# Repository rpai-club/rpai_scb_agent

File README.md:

# Cross Point Project
Software-Configured Breadboard Hardware Targeting Circuit Wiring Error Reduction in ECE Labs.
#
Abstract:
#
The hardware project aims to examine the effectiveness of software-configured wiring compared to traditional manual wiring of breadboards. While both methods use actual hardware, the software-configured approach automates the connections between components, thereby minimizing wiring errors and setup time. The intent is to investigate the impact of each approach on student comprehension, engagement, and error rates. By comparing these two approaches, the project seeks to determine which method better supports student engagement, educational outcomes and reduces frustration associated with complex circuit construction.
#
Introduction:
#
Hands-on experiential learning is a cornerstone of ECE education, typically relying on manual wiring of circuits on solderless breadboards. Using a traditional solderless breadboard as the means for building electronic circuit lab experiments requires the student, in addition to placing components, to manually insert wires to connect together the component pins according to a schematic diagram. These manual translation steps from schematic to hardware can lead to wiring errors in the experimental setup that can obscure circuit principles. While this manual wiring method offers valuable experience in physical component handling and troubleshooting, the extra time needed for debugging and correcting these errors leads to frustration and loss of precious lab time to investigate the circuit concept in question.

The goal is to evaluate the educational benefits and potential drawbacks of these software-configured hardware systems compared to traditional manual wiring. By doing so, it addresses the need for balancing hands-on skills with error minimization and conceptual understanding in electrical engineering education.
#
Analog switch matrix cross point experiment breadboard.
#

Production PCB (Red3 version, instructions for ordering boards can be found in PCB Projects folder)
 
The idea is to computerize the wiring of the breadboard in an effort to reduce student frustration when building complex experiments. Using four analog 16X8 cross point switches wired together into two 32X8 cross points with a fifth switch matrix interconnecting the two smaller arrays into effectively a single 64X16 array.

This breadboard makes real, hardware connections between the 64 breadboard component pins on the board to the16 “jumper” nodes on the board via software commands, instead of needing to manually install jumper wires. The prototype PCB is shown, figure 1, which incorporates two mini 170 pin solderless breadboards, one for each of the 32X8 cross point arrays. There are a combined 68 total component pin locations across both mini breadboards with power distribution strips top and bottom. The two mini breadboards connect to the PCB through pogo pins and so they can be easily removed. It would then be possible to bolt on custom daughter PCBs with whatever components are needed for a given course already installed. Such as CMOS transistor arrays (CD4007) with even some pre-wired sub-circuits like current sources and OTAs.

The combined 64X16 cross point matrix board uses a total of 5 CH446DS 16X8 analog cross point ICs (from China) programed via a RP-2040 micro controller breakout board (Pi Pico or equivalent). Materials cost per board, in quantities of 10 or more, is less than $30 not including the assembly labor.

The board is powered from the Pi Pico USB connection. For powering the experiment circuits, Jumpers can be configured for 0 and +3.3V, 0 and +5V or -5V and +5V power (or 0 and +10V) using an on board isolated 5V DC-DC generator.

LTspice is used to enter the schematic for the experiment. In addition to the standard library symbols a number of supporting schematic library files have been created. Schematic symbols for TO-92 transistors and resistors of various lead spacing are available in the LTspice files.

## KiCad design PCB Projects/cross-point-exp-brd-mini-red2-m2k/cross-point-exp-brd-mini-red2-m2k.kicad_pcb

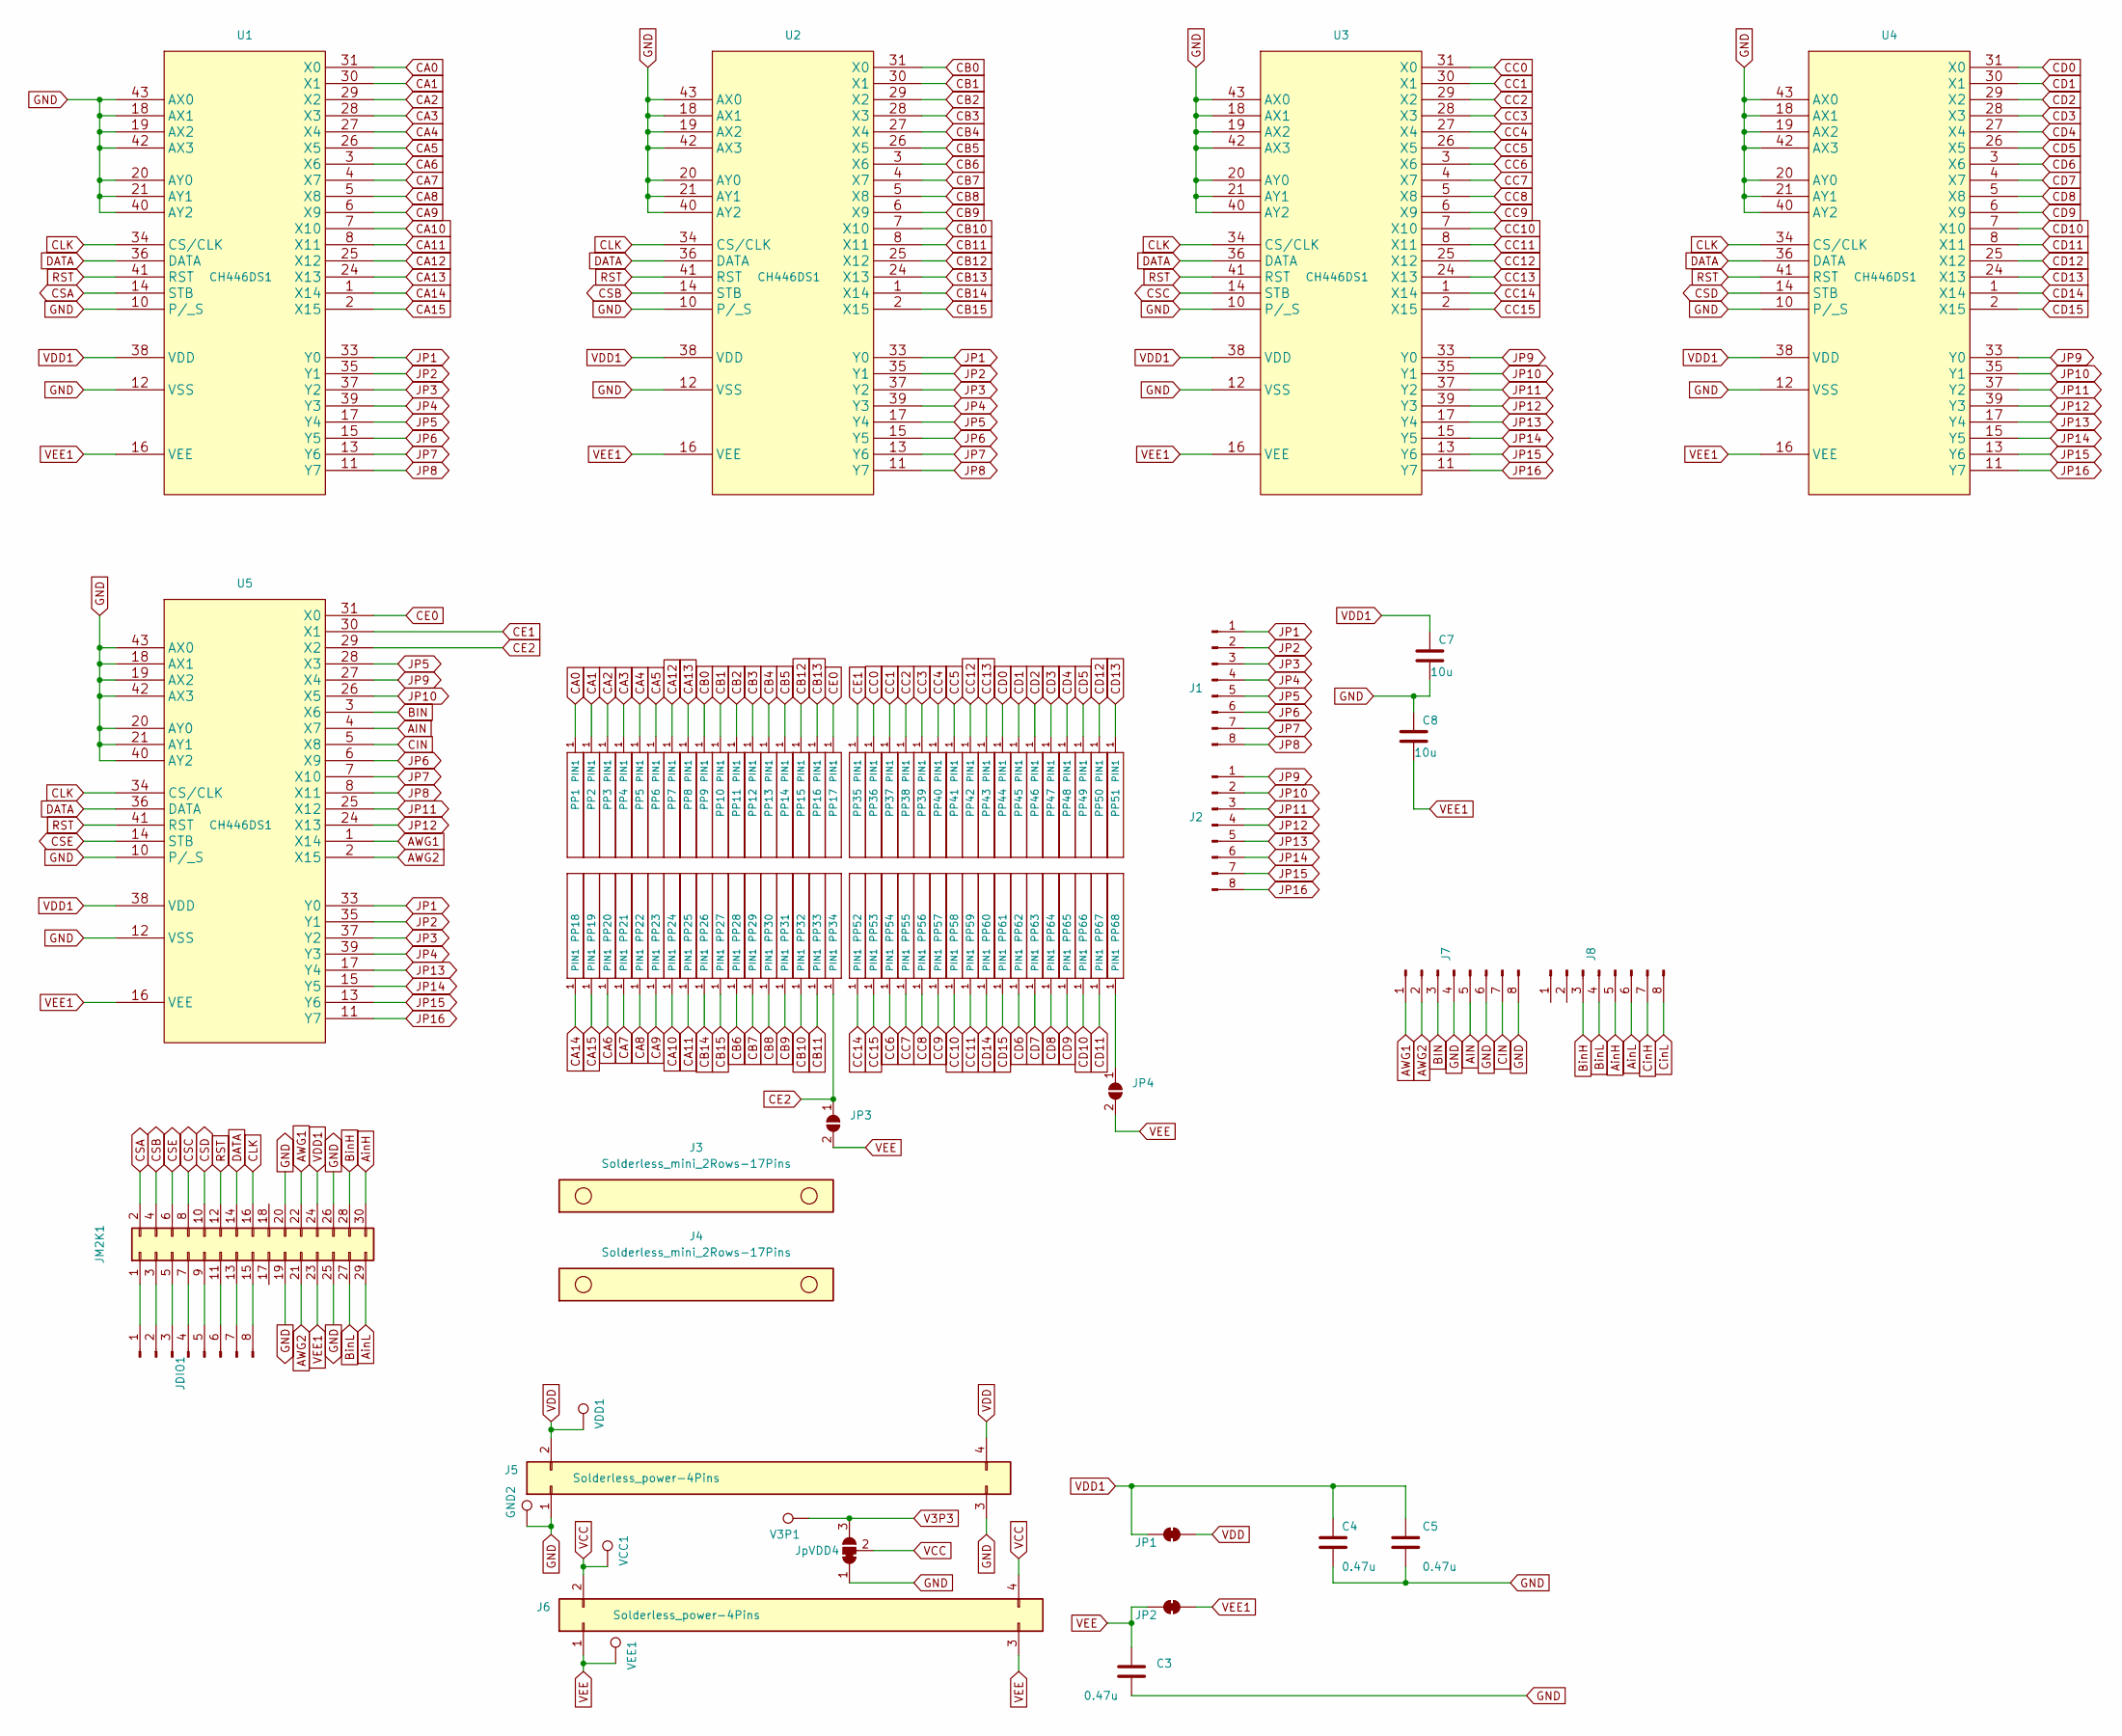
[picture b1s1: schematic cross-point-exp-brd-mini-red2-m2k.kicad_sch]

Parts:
C3, C4, C5: 0.47u; C_1206_3216Metric
C7, C8: 10u; C_1206_3216Metric
GND2: TestPoint; TestPoint_THTPad_D2.0mm_Drill1.0mm
J1, J2, J7, J8: Conn_01x08_Pin; PinHeader_1x08_P2.54mm_Vertical
J3, J4: Solderless_mini_2Rows-17Pins; Solderless_mini_mount_holes_2x17_P2.54mm
J5, J6: Solderless_power-4Pins; Solderless_power_2x4_P2.54mm
JDIO1: Conn_01x08_Pin; PinHeader_1x08_P2.54mm_Vertical
JM2K1: Conn_02x15_Odd_Even; PinHeader_2x15_P2.54mm_Vertical
JP1, JP2: SolderJumper_2_Bridged; SolderJumper-2_P1.3mm_Bridged_RoundedPad1.0x1.5mm
JP3, JP4: SolderJumper_2_Open; SolderJumper-2_P1.3mm_Open_RoundedPad1.0x1.5mm
JpVDD4: Conn_01x03_Pin; SolderJumper-3_P1.3mm_Bridged12_RoundedPad1.0x1.5mm_NumberL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
PP1, PP2, PP3, PP4, PP5, PP6, PP7, PP8, PP9, PP10, PP11, PP12, PP13, PP14, PP15, PP16, PP17, PP18, PP19, PP20, PP21, PP22, PP23, PP24, PP25, PP26, PP27, PP28, PP29, PP30, PP31, PP32, PP33, PP34, PP35, PP36, PP37, PP38, PP39, PP40, PP41, PP42, PP43, PP44, PP45, PP46, PP47, PP48, PP49, PP50, PP51, PP52, PP53, PP54, PP55, PP56, PP57, PP58, PP59, PP60, PP61, PP62, PP63, PP64, PP65, PP66, PP67, PP68: POGO_PIN_01X01_70-9150; MF_Connectors-POGO_PIN_70-9150
U1, U2, U3, U4, U5: CH446DS1; LQFP44_Tight
V3P1: TestPoint; TestPoint_THTPad_D2.0mm_Drill1.0mm
VCC1: TestPoint; TestPoint_THTPad_D2.0mm_Drill1.0mm
VDD1: TestPoint; TestPoint_THTPad_D2.0mm_Drill1.0mm
VEE1: TestPoint; TestPoint_THTPad_D2.0mm_Drill1.0mm

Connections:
AIN: J7.5, U5.4 (X7)
AWG1: J7.1, JM2K1.22, U5.1 (X14)
AWG2: J7.2, JM2K1.21, U5.2 (X15)
AinH: J8.5, JM2K1.30
AinL: J8.6, JM2K1.29
BIN: J7.3, U5.3 (X6)
BinH: J8.3, JM2K1.28
BinL: J8.4, JM2K1.27
CA0: PP1.1 (PIN1), U1.31 (X0)
CA1: PP2.1 (PIN1), U1.30 (X1)
CA2: PP3.1 (PIN1), U1.29 (X2)
CA3: PP4.1 (PIN1), U1.28 (X3)
CA4: PP5.1 (PIN1), U1.27 (X4)
CA5: PP6.1 (PIN1), U1.26 (X5)
CA6: PP20.1 (PIN1), U1.3 (X6)
CA7: PP21.1 (PIN1), U1.4 (X7)
CA8: PP22.1 (PIN1), U1.5 (X8)
CA9: PP23.1 (PIN1), U1.6 (X9)
CA10: PP24.1 (PIN1), U1.7 (X10)
CA11: PP25.1 (PIN1), U1.8 (X11)
CA12: PP7.1 (PIN1), U1.25 (X12)
CA13: PP8.1 (PIN1), U1.24 (X13)
CA14: PP18.1 (PIN1), U1.1 (X14)
CA15: PP19.1 (PIN1), U1.2 (X15)
CB0: PP9.1 (PIN1), U2.31 (X0)
CB1: PP10.1 (PIN1), U2.30 (X1)
CB2: PP11.1 (PIN1), U2.29 (X2)
CB3: PP12.1 (PIN1), U2.28 (X3)
CB4: PP13.1 (PIN1), U2.27 (X4)
CB5: PP14.1 (PIN1), U2.26 (X5)
CB6: PP28.1 (PIN1), U2.3 (X6)
CB7: PP29.1 (PIN1), U2.4 (X7)
CB8: PP30.1 (PIN1), U2.5 (X8)
CB9: PP31.1 (PIN1), U2.6 (X9)
CB10: PP32.1 (PIN1), U2.7 (X10)
CB11: PP33.1 (PIN1), U2.8 (X11)
CB12: PP15.1 (PIN1), U2.25 (X12)
CB13: PP16.1 (PIN1), U2.24 (X13)
CB14: PP26.1 (PIN1), U2.1 (X14)
CB15: PP27.1 (PIN1), U2.2 (X15)
CC0: PP36.1 (PIN1), U3.31 (X0)
CC1: PP37.1 (PIN1), U3.30 (X1)
CC2: PP38.1 (PIN1), U3.29 (X2)
CC3: PP39.1 (PIN1), U3.28 (X3)
CC4: PP40.1 (PIN1), U3.27 (X4)
CC5: PP41.1 (PIN1), U3.26 (X5)
CC6: PP54.1 (PIN1), U3.3 (X6)
CC7: PP55.1 (PIN1), U3.4 (X7)
CC8: PP56.1 (PIN1), U3.5 (X8)
CC9: PP57.1 (PIN1), U3.6 (X9)
CC10: PP58.1 (PIN1), U3.7 (X10)
CC11: PP59.1 (PIN1), U3.8 (X11)
CC12: PP42.1 (PIN1), U3.25 (X12)
CC13: PP43.1 (PIN1), U3.24 (X13)
CC14: PP52.1 (PIN1), U3.1 (X14)
CC15: PP53.1 (PIN1), U3.2 (X15)
CD0: PP44.1 (PIN1), U4.31 (X0)
CD1: PP45.1 (PIN1), U4.30 (X1)
CD2: PP46.1 (PIN1), U4.29 (X2)
CD3: PP47.1 (PIN1), U4.28 (X3)
CD4: PP48.1 (PIN1), U4.27 (X4)
CD5: PP49.1 (PIN1), U4.26 (X5)
CD6: PP62.1 (PIN1), U4.3 (X6)
CD7: PP63.1 (PIN1), U4.4 (X7)
CD8: PP64.1 (PIN1), U4.5 (X8)
CD9: PP65.1 (PIN1), U4.6 (X9)
CD10: PP66.1 (PIN1), U4.7 (X10)
CD11: PP67.1 (PIN1), U4.8 (X11)
CD12: PP50.1 (PIN1), U4.25 (X12)
CD13: PP51.1 (PIN1), U4.24 (X13)
CD14: PP60.1 (PIN1), U4.1 (X14)
CD15: PP61.1 (PIN1), U4.2 (X15)
CE0: PP17.1 (PIN1), U5.31 (X0)
CE1: PP35.1 (PIN1), U5.30 (X1)
CE2: JP3.1 (A), PP34.1 (PIN1), U5.29 (X2)
CIN: J7.7, U5.5 (X8)
CLK: JM2K1.16, U1.34 (CS/CLK), U2.34 (CS/CLK), U3.34 (CS/CLK), U4.34 (CS/CLK), U5.34 (CS/CLK)
CSA: JM2K1.2, U1.14 (STB)
CSB: JM2K1.4, U2.14 (STB)
CSC: JM2K1.8, U3.14 (STB)
CSD: JM2K1.10, U4.14 (STB)
CSE: JM2K1.6, U5.14 (STB)
CinH: J8.7
CinL: J8.8
DATA: JM2K1.14, U1.36 (DATA), U2.36 (DATA), U3.36 (DATA), U4.36 (DATA), U5.36 (DATA)
GND: C3.2, C4.2, C5.2, C7.2, C8.1, GND2.1, J5.1, J5.3, J7.4, J7.6, J7.8, JM2K1.19, JM2K1.20, JM2K1.25, JM2K1.26, JpVDD4.1 (A), U1.10 (P/_S), U1.12 (VSS), U1.18 (AX1), U1.19 (AX2), U1.20 (AY0), U1.21 (AY1), U1.40 (AY2), U1.42 (AX3), U1.43 (AX0), U2.10 (P/_S), U2.12 (VSS), U2.18 (AX1), U2.19 (AX2), U2.20 (AY0), U2.21 (AY1), U2.40 (AY2), U2.42 (AX3), U2.43 (AX0), U3.10 (P/_S), U3.12 (VSS), U3.18 (AX1), U3.19 (AX2), U3.20 (AY0), U3.21 (AY1), U3.40 (AY2), U3.42 (AX3), U3.43 (AX0), U4.10 (P/_S), U4.12 (VSS), U4.18 (AX1), U4.19 (AX2), U4.20 (AY0), U4.21 (AY1), U4.40 (AY2), U4.42 (AX3), U4.43 (AX0), U5.10 (P/_S), U5.12 (VSS), U5.18 (AX1), U5.19 (AX2), U5.20 (AY0), U5.21 (AY1), U5.40 (AY2), U5.42 (AX3), U5.43 (AX0); also elsewhere on the board
JP1: J1.1, U1.33 (Y0), U2.33 (Y0), U5.33 (Y0)
JP2: J1.2, U1.35 (Y1), U2.35 (Y1), U5.35 (Y1)
JP3: J1.3, U1.37 (Y2), U2.37 (Y2), U5.37 (Y2)
JP4: J1.4, U1.39 (Y3), U2.39 (Y3), U5.39 (Y3)
JP5: J1.5, U1.17 (Y4), U2.17 (Y4), U5.28 (X3)
JP6: J1.6, U1.15 (Y5), U2.15 (Y5), U5.6 (X9)
JP7: J1.7, U1.13 (Y6), U2.13 (Y6), U5.7 (X10)
JP8: J1.8, U1.11 (Y7), U2.11 (Y7), U5.8 (X11)
JP9: J2.1, U3.33 (Y0), U4.33 (Y0), U5.27 (X4)
JP10: J2.2, U3.35 (Y1), U4.35 (Y1), U5.26 (X5)
JP11: J2.3, U3.37 (Y2), U4.37 (Y2), U5.25 (X12)
JP12: J2.4, U3.39 (Y3), U4.39 (Y3), U5.24 (X13)
JP13: J2.5, U3.17 (Y4), U4.17 (Y4), U5.17 (Y4)
JP14: J2.6, U3.15 (Y5), U4.15 (Y5), U5.15 (Y5)
JP15: J2.7, U3.13 (Y6), U4.13 (Y6), U5.13 (Y6)
JP16: J2.8, U3.11 (Y7), U4.11 (Y7), U5.11 (Y7)
unnamed: JDIO1.1, JM2K1.1
unnamed: JDIO1.2, JM2K1.3
unnamed: JDIO1.3, JM2K1.5
unnamed: JDIO1.4, JM2K1.7
unnamed: JDIO1.5, JM2K1.9
unnamed: JDIO1.6, JM2K1.11
unnamed: JDIO1.7, JM2K1.13
unnamed: JDIO1.8, JM2K1.15
unnamed: JP4.1 (A), PP68.1 (PIN1)
RST: JM2K1.12, U1.41 (RST), U2.41 (RST), U3.41 (RST), U4.41 (RST), U5.41 (RST)
V3P3: JpVDD4.3 (B), V3P1.1
VCC: J6.2, J6.4, JpVDD4.2 (C), VCC1.1
VDD: J5.2, J5.4, JP1.1 (A), VDD1.1
VDD1: C4.1, C5.1, C7.1, JM2K1.24, JP1.2 (B), U1.38 (VDD), U2.38 (VDD), U3.38 (VDD), U4.38 (VDD), U5.38 (VDD)
VEE: C3.1, J6.1, J6.3, JP2.2 (B), JP3.2 (B), JP4.2 (B), VEE1.1
VEE1: C8.2, JM2K1.23, JP2.1 (A), U1.16 (VEE), U2.16 (VEE), U3.16 (VEE), U4.16 (VEE), U5.16 (VEE)

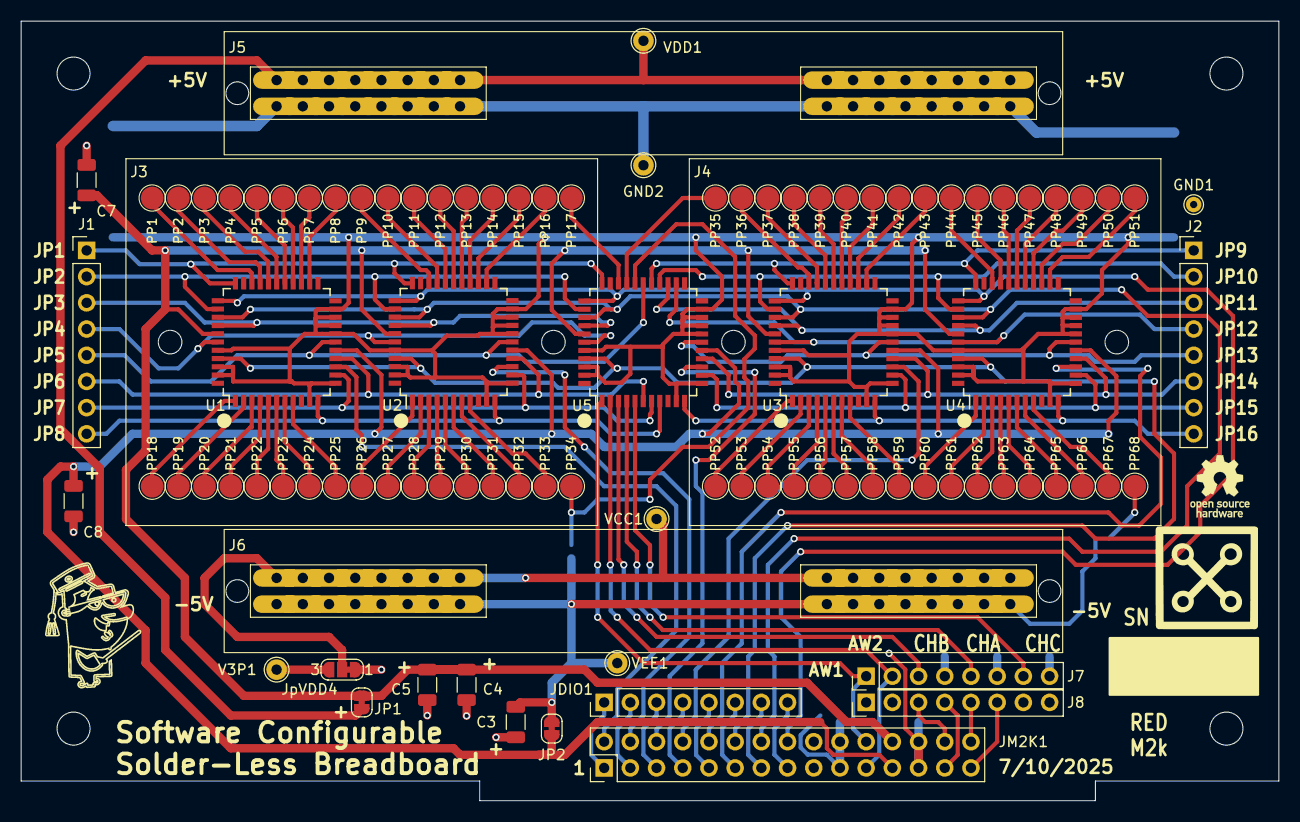
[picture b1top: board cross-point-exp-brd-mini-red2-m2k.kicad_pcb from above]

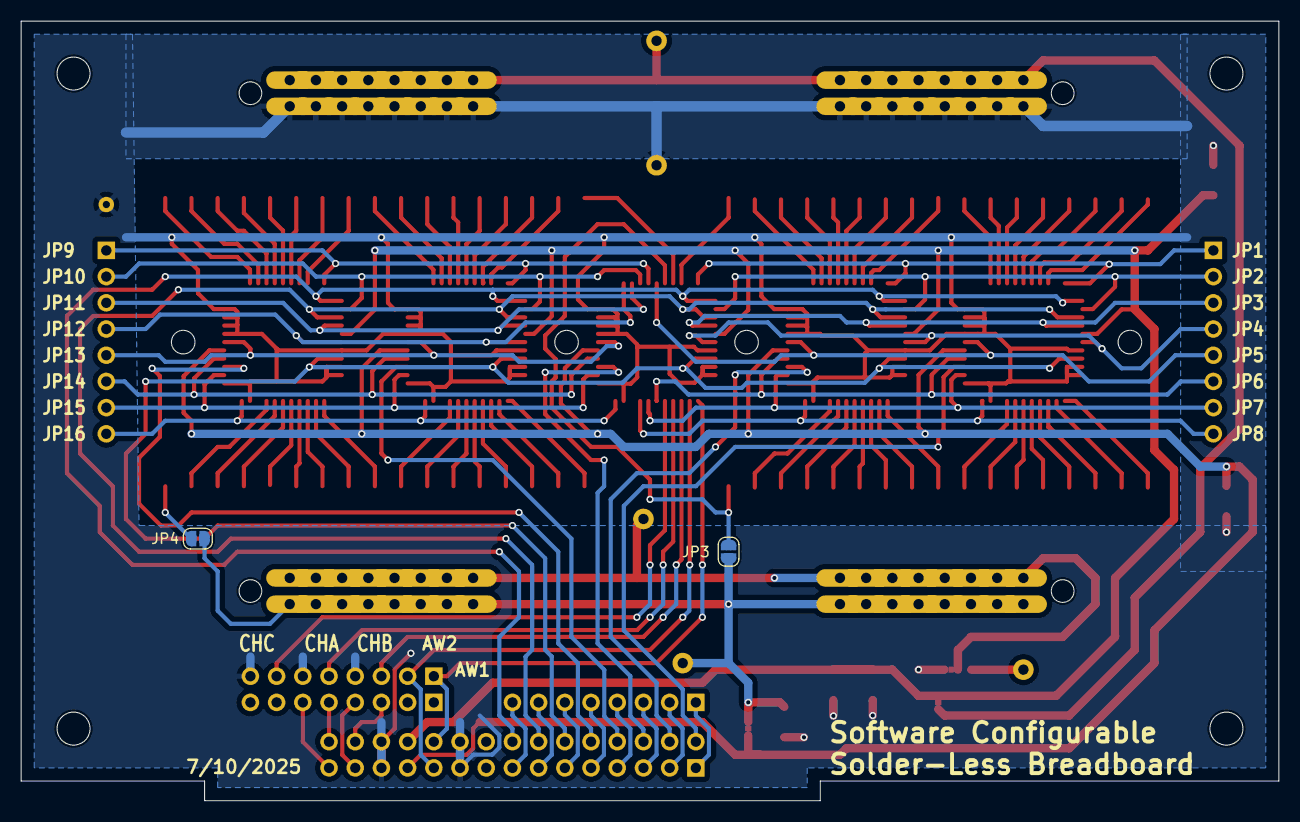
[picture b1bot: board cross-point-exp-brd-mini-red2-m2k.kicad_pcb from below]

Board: 2 copper layers, 121.9 x 75.6 mm, 99 parts (2 on the bottom side), 116 nets.

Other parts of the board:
GND1: TestPoint; TestPoint_THTPad_D1.5mm_Drill0.7mm

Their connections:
GND: GND1.1; also elsewhere on the board

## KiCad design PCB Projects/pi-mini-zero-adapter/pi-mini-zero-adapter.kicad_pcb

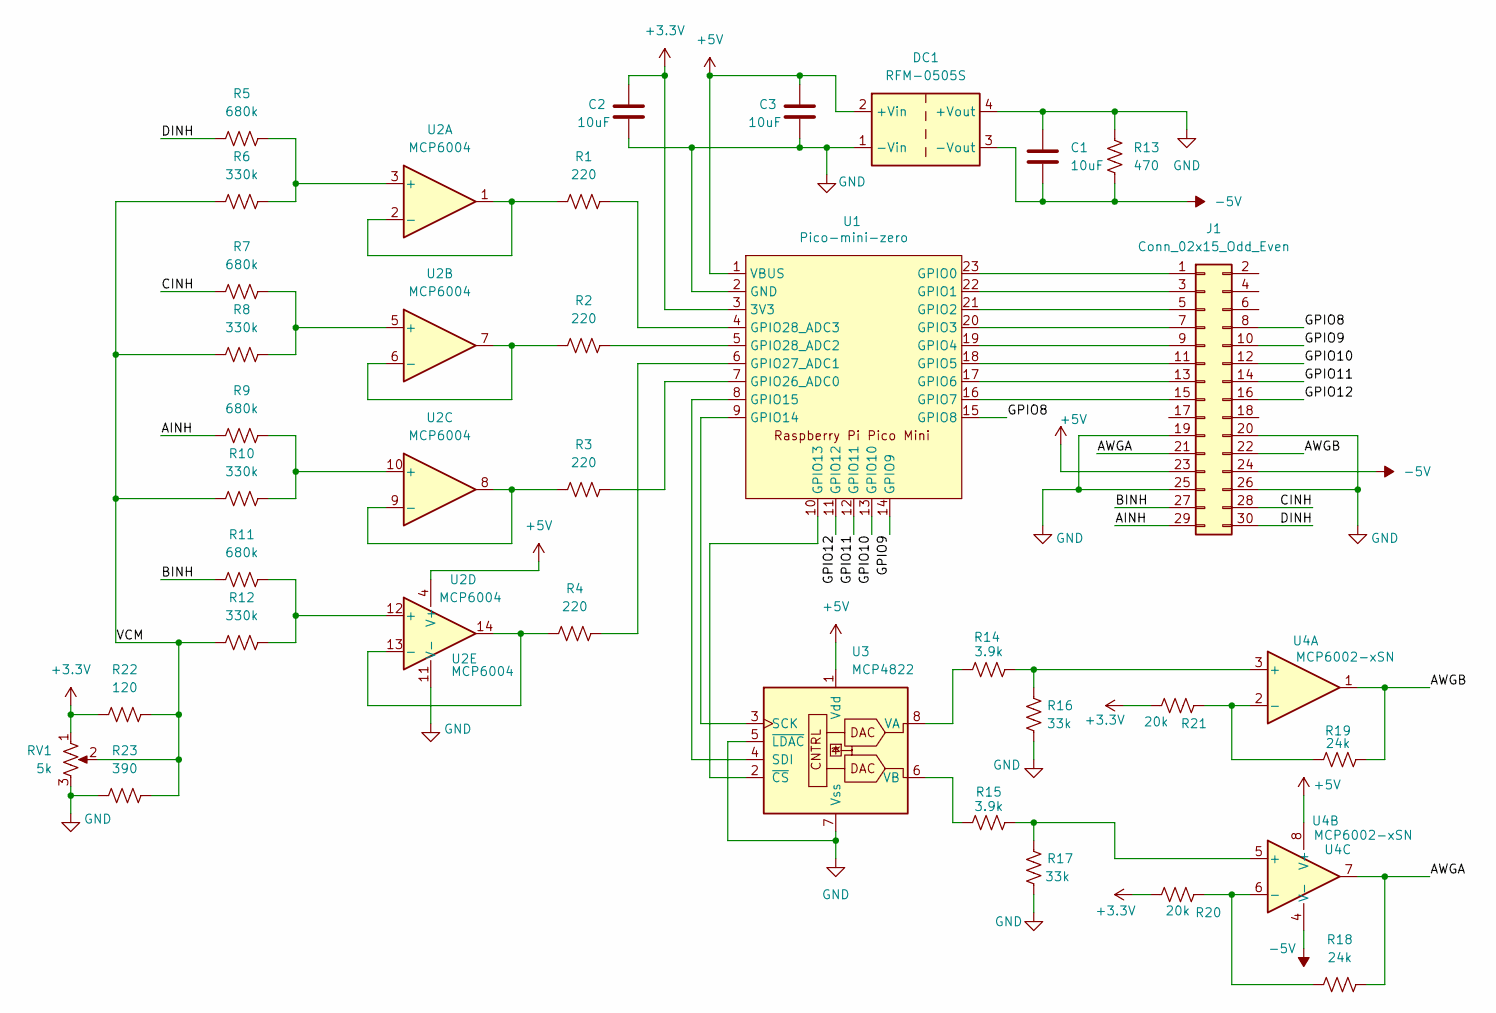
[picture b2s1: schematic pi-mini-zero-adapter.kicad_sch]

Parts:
C1, C2, C3: 10uF; C_1206_3216Metric
DC1: RFM-0505S
J1: Conn_02x15_Odd_Even; PinHeader_2x15_P2.54mm_Horizontal
R1, R2, R3, R4: 220; R_1206_3216Metric
R5, R7, R9, R11: 680k; R_1206_3216Metric
R6, R8, R10, R12: 330k; R_1206_3216Metric
R13: 470; R_1206_3216Metric
R14, R15: 3.9k; R_1206_3216Metric
R16, R17: 33k; R_1206_3216Metric
R18, R19: 24k; R_1206_3216Metric
R20, R21: 20k; R_1206_3216Metric
R22: 120; R_1206_3216Metric
R23: 390; R_1206_3216Metric
RV1: 5k; Potentiometer_Bourns_3386P_Vertical
U1: Pico-mini-zero; RPi_Mini_Zero_SMD_TH
U2: MCP6004; SOIC-14_3.9x8.7mm_P1.27mm
U3: MCP4822; SOIC-8_3.9x4.9mm_P1.27mm
U4: MCP6002-xSN; SO-8_3.9x4.9mm_P1.27mm

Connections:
+3.3V: C2.1, R20.2, R21.2, R22.2, RV1.1, U1.3 (3V3)
+5V: C3.1, DC1.2 (+Vin), J1.23, U1.1 (VBUS), U2.4 (V+), U3.1 (Vdd), U4.8 (V+)
-5V: C1.2, DC1.3 (-Vout), J1.24, R13.2, U4.4 (V-)
/AINH: J1.29, R9.2
/AWGA: J1.21, R18.1, U4.7
/AWGB: J1.22, R19.1, U4.1
/BINH: J1.27, R11.2
/CINH: J1.28, R7.2
/DINH: J1.30, R5.2
/GPIO8: J1.8, U1.15 (GPIO8)
/GPIO9: J1.10, U1.14 (GPIO9)
/GPIO10: J1.12, U1.13 (GPIO10)
/GPIO11: J1.14, U1.12 (GPIO11)
/GPIO12: J1.16, U1.11 (GPIO12)
/VCM: R6.2, R8.2, R10.2, R12.2, R22.1, R23.1, RV1.2
GND: C1.1, C2.2, C3.2, DC1.1 (-Vin), DC1.4 (+Vout), J1.19, J1.20, J1.25, J1.26, R13.1, R16.1, R17.1, R23.2, RV1.3, U1.2 (GND), U2.11 (V-), U3.5 (~LDAC), U3.7 (Vss)
unnamed: J1.1, U1.23 (GPIO0)
unnamed: J1.3, U1.22 (GPIO1)
unnamed: J1.5, U1.21 (GPIO2)
unnamed: J1.7, U1.20 (GPIO3)
unnamed: J1.9, U1.19 (GPIO4)
unnamed: J1.11, U1.18 (GPIO5)
unnamed: J1.13, U1.17 (GPIO6)
unnamed: J1.15, U1.16 (GPIO7)
unnamed: U1.10 (GPIO13), U3.2 (~CS)
unnamed: U1.9 (GPIO14), U3.3 (SCK)
unnamed: U1.8 (GPIO15), U3.4 (SDI)
unnamed: R3.1, U1.7 (GPIO26_ADC0)
unnamed: R4.1, U1.6 (GPIO27_ADC1)
unnamed: R2.1, U1.5 (GPIO28_ADC2)
unnamed: R1.1, U1.4 (GPIO28_ADC3)
unnamed: R5.1, R6.1, U2.3 (+)
unnamed: R1.2, U2.1, U2.2 (-)
unnamed: R7.1, R8.1, U2.5 (+)
unnamed: R2.2, U2.6 (-), U2.7
unnamed: R9.1, R10.1, U2.10 (+)
unnamed: R3.2, U2.8, U2.9 (-)
unnamed: R11.1, R12.1, U2.12 (+)
unnamed: R4.2, U2.13 (-), U2.14
unnamed: R14.2, U3.8 (VA)
unnamed: R15.2, U3.6 (VB)
unnamed: R14.1, R16.2, U4.3 (+)
unnamed: R19.2, R21.1, U4.2 (-)
unnamed: R15.1, R17.2, U4.5 (+)
unnamed: R18.2, R20.1, U4.6 (-)

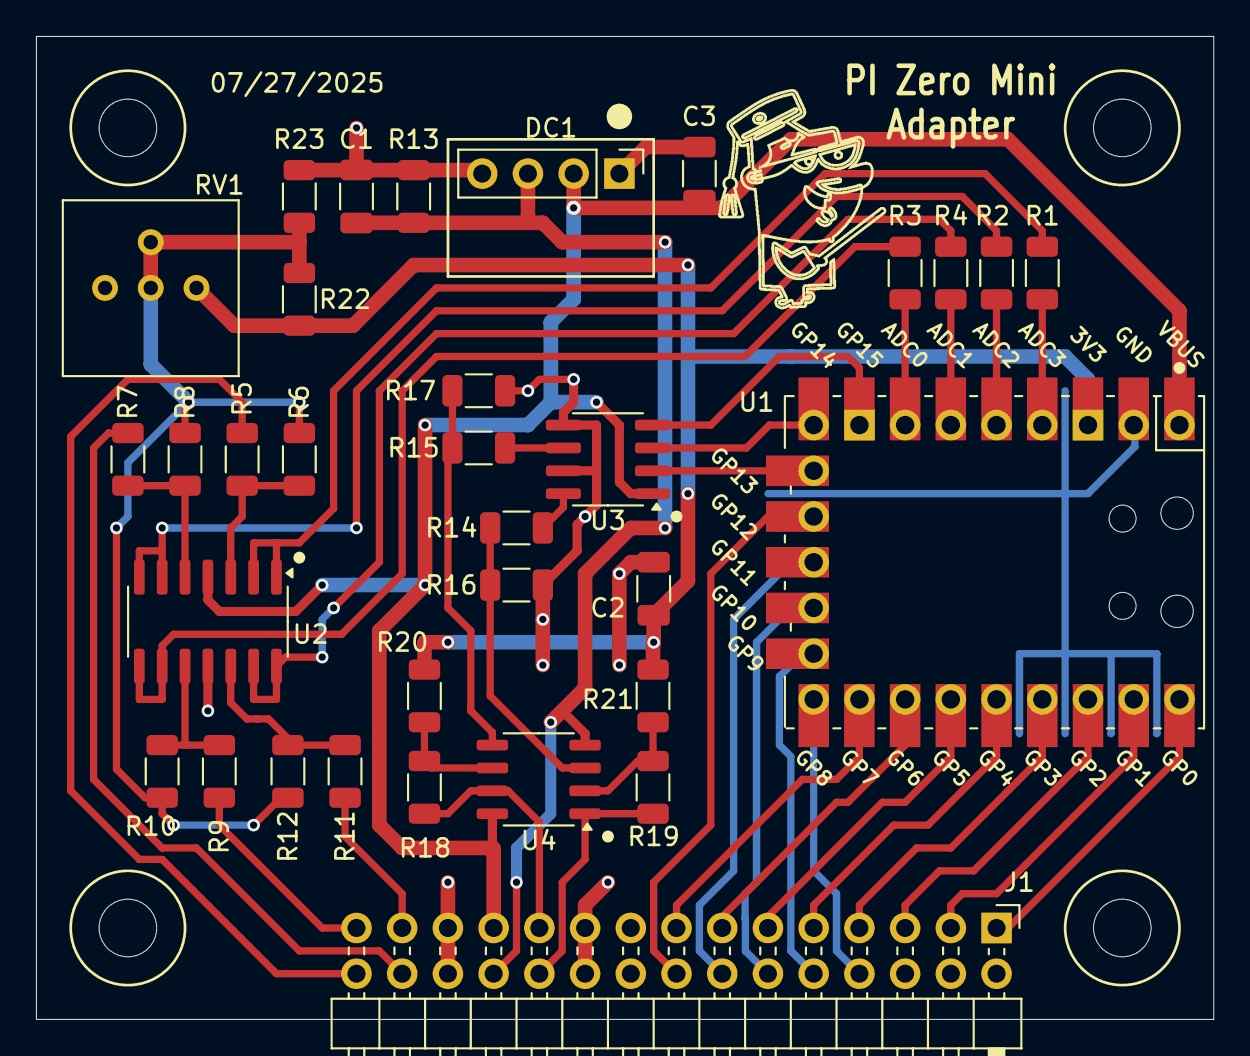
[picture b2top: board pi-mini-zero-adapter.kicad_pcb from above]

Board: 2 copper layers, 65.4 x 54.6 mm, 33 parts (0 on the bottom side), 45 nets.

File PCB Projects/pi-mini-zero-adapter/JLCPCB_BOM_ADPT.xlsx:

Comment | Designator | Footprint | JLCPCB Part#(optional)
10uF | C1,C2,C3 | 1206 | C1849
330KΩ | R6,R8,R10,R12 | 1206 | C17929
680KΩ | R5,R7,R9,R11 | 1206 | C17974
3.9k | R14,R15 | 1206 | C17883
33k | R16,R17 | 1206 | C18004
24k | R18,R19 | 1206 | C17960
20k | R20,R21 | 1206 | C18003
120Ω | R22 | 1206 | C17909
390Ω | R1,R2,R3,R4,R13,R23 | 1206 | C4491
MC33202DR2G | U4 | SOIC-8 | C43122
MCP4822-E/SN | U3 | SOIC-8 | C16040
MCP6004T-I/SL | U2 | SOIC-14 | C7378

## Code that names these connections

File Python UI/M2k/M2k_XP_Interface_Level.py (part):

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JP5 = "CE3"; JP6 = "CE9"; JP7 = "CE10"; JP8 = "CE11"
JP9 = "CE4"; JP10 = "CE5"; JP11 = "CE12"; JP12 = "CE13"
# Change these serial pins to match board layout
CSA = 7; CSB = 6; CSE = 5; CSC = 4; CSD = 3; RST = 2; DATA = 1; CLK = 0
#
JumperSpinBoxList = ("JP1", "JP2", "JP3", "JP4", "JP5", "JP6", "JP7", "JP8",
                     "JP9", "JP10", "JP11", "JP12", "JP13", "JP14", "JP15", "JP16")
CompSpinBoxList = ("AWG1", "AWG2", "AINH", "BINH", "CINH")
#
# Cross point matrix functions
#
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
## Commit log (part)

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2025-02-17 Python Ui improvement
    LTspice net list reader now able to read both .cir and .net versions of LTspice net lists.
2025-02-23 Add Assembly Videos
    Added two videos showing how to bend the power rail jumpers.
2025-04-05 Add new SMD PCB design files
    Add new KiCAD project for mostly SMD version of the board.
2025-04-12 JLCPCB Test Run Project files
    The KiCAD project folder for the Red2 SMD pcb layout with solder jumpers now contains the JLCPCB Gerber, BOM and component placement files for board assembly at JLCPCB.
2025-05-19 Python code updates
    Bug fixes to main ALICE code and hardware code for original through hole Red boards. Adding new hardware code for surface mound Red boards and first pass at self test function.
2025-06-03 Add PCB built instructions
    This update adds instructions to build PCBs at JLCPCB. Also improvements to Python UI and some additional example LTspice schematics.
2025-06-05 Add read me file to Python UI
    Adds a read me file for the Python UI and fixes a couple of minor typos.
2025-06-05 Update README.md
    Try again.
2025-06-16 Adding LTspice examples
    Adding a number of digital LTspice example schematics and fixes to Red board python configuration files.
2025-07-18 M2k Python Code first release
    This is the first release of libm2k Pyhton code to control a cross point board.
2025-08-01 Changes to fix LTspice netlist changes
    These changes are mainly to make the code compatible with the way LTspice netlists in 24.1.9 and newer.
2025-08-02 Even more corrections for LTSpice netlisting
    Another change is required by changes to the way LTspice 24.1.9 creates net lists.
2025-08-02 Yet another attempt to fix LTspice 24.1.9 net lists
    Hopefully this is the final fix to the LTspice 24.1.9 net listing problem.
2025-09-01 Add Rekeases
    Adds special RPI Bundle archive to Releases folder.
2025-10-01 Create RPI Bundle-oct-2025.zip
    October release with advanced placement functions.
2025-11-02 November release of RPI bundle
    This is the November User interface release. It also includes updated versions for the M2k / Scopy adapter version of the SCB.
2025-11-17 Create RPI Bundle-nov-17.zip
    Nov release needed fixes to make self-cal and self test work again with new manual set reset matrix buttons
2026-01-15 January 2026 release of project files
    This is the January project files release ahead of Spring semester. Includes files for RED3 version of the hardware.
2026-03-10 rudementary cross point adder
2026-03-15 ECEDHA Demo
    Add zip of files for ECEDHA 2026 software demo
2026-03-23 Revert launcher back to .pyw (no console window)
2026-03-31 added function to display user and ai output
2026-03-31 added resize functionality to chatbox
2026-04-12 Create RPI-bundle-April-2026.zip
    Archive of software file as of April 12 2026.

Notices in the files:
Python UI/M2k/M2k_XP_Interface_Level.py:
TR2 = "CC0"; TR3 = "CC1"; TR4 = "CC2"; TR5 = "CC3"; TR6 = "CC4"; TR7 = "CC5"; TR8 = "CC12"; TR9 = "CC13"
